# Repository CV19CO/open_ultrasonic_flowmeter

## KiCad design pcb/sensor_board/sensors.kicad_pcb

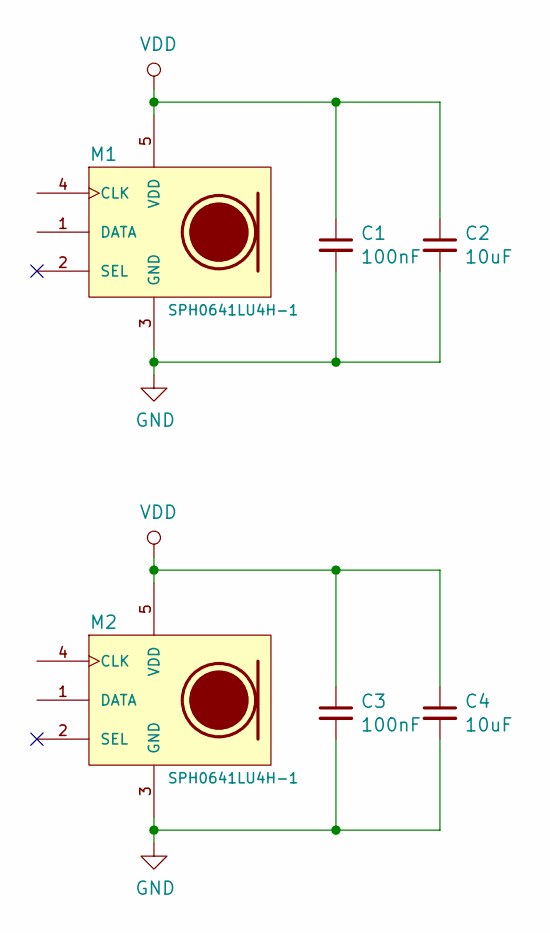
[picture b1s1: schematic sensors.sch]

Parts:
C1, C3: 100nF; C_0402_1005Metric
C2, C4: 10uF; C_0603_1608Metric
M1, M2: SPH0641LU4H-1; MIC_SPH0641LU4H-1

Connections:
GND: C1.2, C2.2, C3.2, C4.2, M1.3 (GND), M2.3 (GND)
VDD: C1.1, C2.1, C3.1, C4.1, M1.5 (VDD), M2.5 (VDD)

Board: 2 copper layers, 6 parts (0 on the bottom side), 2 nets, no tracks yet.

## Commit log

2020-04-09 first clean-up
